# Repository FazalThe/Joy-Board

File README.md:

# Joy Board

A custom-built split keyboard with a built in thumb joystick on the left side, runs on zmk firmware and also supports zmk studio. The joystick is inteded to use the movements as key presses, but later is when I realised that it's really good for gaming( I don't really game, maybe thats why).

---

##  Features

-  Split Ergonomic Layout
- Thumb Joystick (Left Side)
- ZMK Studio 

---

## Schematic

---

##  PCB 

---

## Case

## BOM
- 2x Pro Micro nRF52840
- 50 x 1N5819 SMD Diodes
- 50 x MX-Style switches (and keycaps)
- 1  x COM-09032
- 2  x JST PH 2pin
- 8  x 10k ohm 0805 resistor
- 4  x 22k ohm 0805 resistor
- 4  x 2.4k ohm 0805 resistor
- 4  x LM339 - SOIC14
- 2  x 100-400 MaH li-po battery
- 4  x 4mm M2 Heatset insert
- 14 x 6mm M2 Heatset insert
- 4  x 6mm M2 Screws
- 14 x 8mm M2 Screws

---

## Credits

- Cherry MX keycap 3D model from [GrabCAD](https://grabcad.com/library/cherry-mx-keycaps-1).

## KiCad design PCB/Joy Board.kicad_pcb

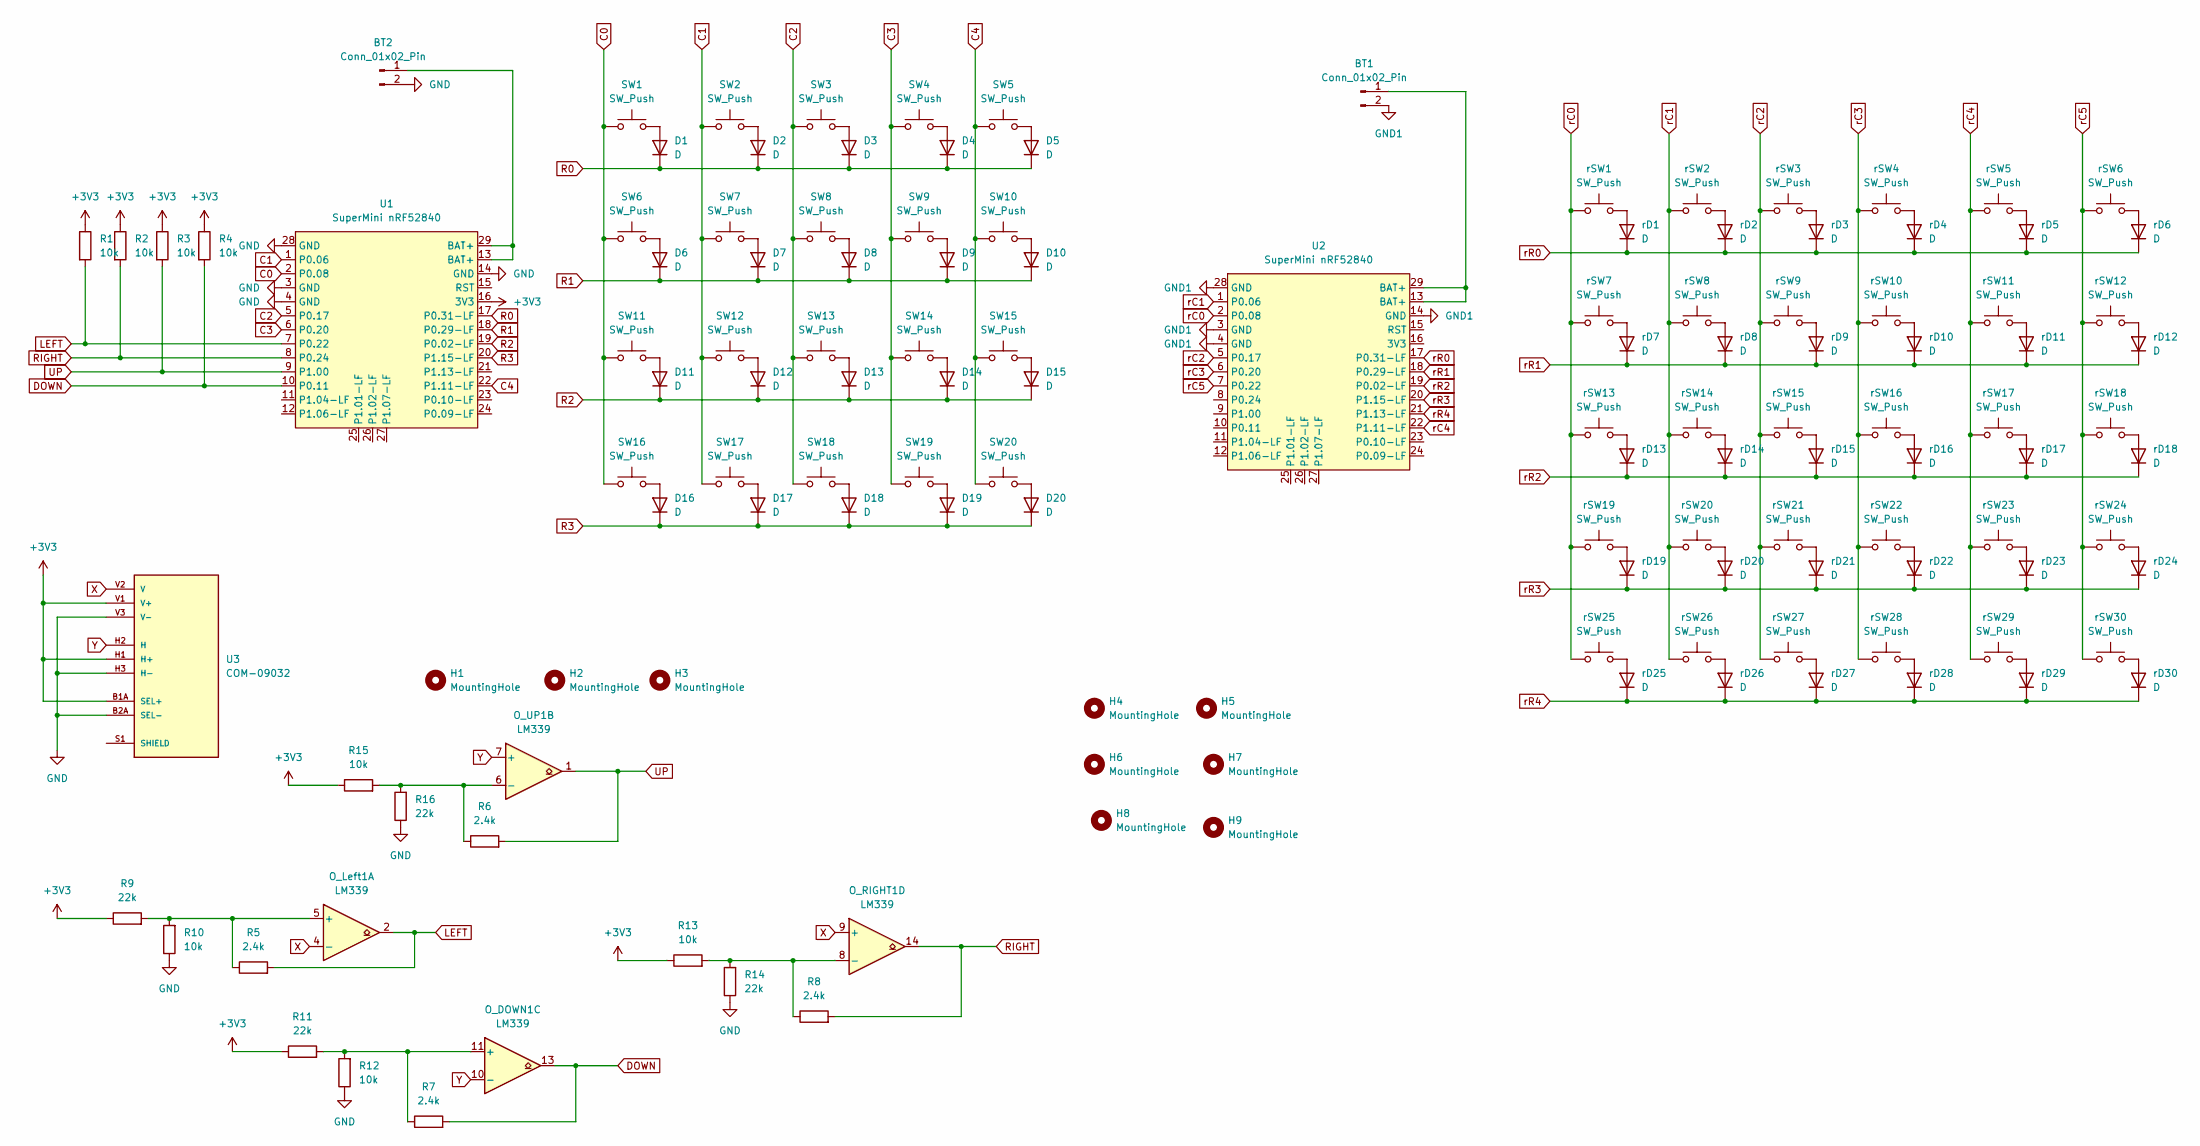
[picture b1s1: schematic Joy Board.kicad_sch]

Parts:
BT1, BT2: Conn_01x02_Pin; JST_PH_S2B-PH-K_1x02_P2.00mm_Horizontal
D1, D2, D3, D4, D5, D6, D7, D8, D9, D10, D11, D12, D13, D14, D15, D16, D17, D18, D19, D20: D; D_SOD-123
H1, H2, H3: MountingHole; mouse-bite-5mm-slot
H4, H5, H6, H7, H8, H9: MountingHole; MountingHole_2.2mm_M2
O_DOWN1: LM339; SOIC-14_3.9x8.7mm_P1.27mm
O_Left1: LM339; SOIC-14_3.9x8.7mm_P1.27mm
O_RIGHT1: LM339; SOIC-14_3.9x8.7mm_P1.27mm
O_UP1: LM339; SOIC-14_3.9x8.7mm_P1.27mm
R1, R2, R3, R4, R10, R12, R13, R15: 10k; R_0805_2012Metric_Pad1.20x1.40mm_HandSolder
R5, R6, R7, R8: 2.4k; R_0805_2012Metric_Pad1.20x1.40mm_HandSolder
R9, R11, R14, R16: 22k; R_0805_2012Metric_Pad1.20x1.40mm_HandSolder
SW1, SW2, SW3, SW4, SW5, SW6, SW7, SW8, SW9, SW10, SW11, SW12, SW13, SW14, SW15, SW16, SW17, SW18, SW19, SW20: SW_Push; SW_Cherry_MX_1.00u_PCB_3d
U1, U2: SuperMini nRF52840; SuperMini_nRF52840_AH_USBup
U3: COM-09032; XDCR_COM-09032; PARTREV N/A
rD1, rD2, rD3, rD4, rD5, rD6, rD7, rD8, rD9, rD10, rD11, rD12, rD13, rD14, rD15, rD16, rD17, rD18, rD19, rD20, rD21, rD22, rD23, rD24, rD25, rD26, rD27, rD28, rD29, rD30: D; D_SOD-123
rSW1, rSW2, rSW3, rSW4, rSW5, rSW6, rSW7, rSW8, rSW9, rSW10, rSW11, rSW12, rSW13, rSW14, rSW15, rSW16, rSW17, rSW18, rSW19, rSW20, rSW21, rSW22, rSW23, rSW24, rSW25, rSW26, rSW27, rSW28, rSW29: SW_Push; SW_Cherry_MX_1.00u_PCB_3d
rSW30: SW_Push; SW_Cherry_MX_1.50u_PCB

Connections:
+3V3: R1.1, R2.1, R3.1, R4.1, R9.1, R11.1, R13.1, R15.1, U1.16 (3V3), U3.B1A (SEL+), U3.H1 (H+), U3.V1 (V+)
C0: SW1.1, SW6.1, SW11.1, SW16.1, U1.2 (P0.08)
C1: SW2.1, SW7.1, SW12.1, SW17.1, U1.1 (P0.06)
C2: SW3.1, SW8.1, SW13.1, SW18.1, U1.5 (P0.17)
C3: SW4.1, SW9.1, SW14.1, SW19.1, U1.6 (P0.20)
C4: SW5.1, SW10.1, SW15.1, SW20.1, U1.22 (P1.11-LF)
DOWN: O_DOWN1.13, R4.2, R7.2, U1.10 (P0.11)
GND: BT2.2, R10.1, R12.1, R14.1, R16.1, U1.3 (GND), U1.4 (GND), U1.14 (GND), U1.28 (GND), U3.B2A (SEL-), U3.H3 (H-), U3.V3 (V-)
GND1: BT1.2, U2.3 (GND), U2.4 (GND), U2.14 (GND), U2.28 (GND)
LEFT: O_Left1.2, R1.2, R5.2, U1.7 (P0.22)
unnamed: BT1.1, U2.13 (BAT+), U2.29 (BAT+)
unnamed: BT2.1, U1.13 (BAT+), U1.29 (BAT+)
unnamed: D1.2 (A), SW1.2
unnamed: D2.2 (A), SW2.2
unnamed: D3.2 (A), SW3.2
unnamed: D4.2 (A), SW4.2
unnamed: D5.2 (A), SW5.2
unnamed: D6.2 (A), SW6.2
unnamed: D7.2 (A), SW7.2
unnamed: D8.2 (A), SW8.2
unnamed: D9.2 (A), SW9.2
unnamed: D10.2 (A), SW10.2
unnamed: D11.2 (A), SW11.2
unnamed: D12.2 (A), SW12.2
unnamed: D13.2 (A), SW13.2
unnamed: D14.2 (A), SW14.2
unnamed: D15.2 (A), SW15.2
unnamed: D16.2 (A), SW16.2
unnamed: D17.2 (A), SW17.2
unnamed: D18.2 (A), SW18.2
unnamed: D19.2 (A), SW19.2
unnamed: D20.2 (A), SW20.2
unnamed: O_DOWN1.11 (+), R7.1, R11.2, R12.2
unnamed: O_Left1.5 (+), R5.1, R9.2, R10.2
unnamed: O_RIGHT1.8 (-), R8.1, R13.2, R14.2
unnamed: O_UP1.6 (-), R6.1, R15.2, R16.2
unnamed: U3.S1 (SHIELD), U3.S2 (SHIELD), U3.S3 (SHIELD), U3.S4 (SHIELD)
unnamed: rD1.2 (A), rSW1.2
unnamed: rD2.2 (A), rSW2.2
unnamed: rD3.2 (A), rSW3.2
unnamed: rD4.2 (A), rSW4.2
unnamed: rD5.2 (A), rSW5.2
unnamed: rD6.2 (A), rSW6.2
unnamed: rD7.2 (A), rSW7.2
unnamed: rD8.2 (A), rSW8.2
unnamed: rD9.2 (A), rSW9.2
unnamed: rD10.2 (A), rSW10.2
unnamed: rD11.2 (A), rSW11.2
unnamed: rD12.2 (A), rSW12.2
unnamed: rD13.2 (A), rSW13.2
unnamed: rD14.2 (A), rSW14.2
unnamed: rD15.2 (A), rSW15.2
unnamed: rD16.2 (A), rSW16.2
unnamed: rD17.2 (A), rSW17.2
unnamed: rD18.2 (A), rSW18.2
unnamed: rD19.2 (A), rSW19.2
unnamed: rD20.2 (A), rSW20.2
unnamed: rD21.2 (A), rSW21.2
unnamed: rD22.2 (A), rSW22.2
unnamed: rD23.2 (A), rSW23.2
unnamed: rD24.2 (A), rSW24.2
unnamed: rD25.2 (A), rSW25.2
unnamed: rD26.2 (A), rSW26.2
unnamed: rD27.2 (A), rSW27.2
unnamed: rD28.2 (A), rSW28.2
unnamed: rD29.2 (A), rSW29.2
unnamed: rD30.2 (A), rSW30.2
R0: D1.1 (K), D2.1 (K), D3.1 (K), D4.1 (K), D5.1 (K), U1.17 (P0.31-LF)
R1: D6.1 (K), D7.1 (K), D8.1 (K), D9.1 (K), D10.1 (K), U1.18 (P0.29-LF)
R2: D11.1 (K), D12.1 (K), D13.1 (K), D14.1 (K), D15.1 (K), U1.19 (P0.02-LF)
R3: D16.1 (K), D17.1 (K), D18.1 (K), D19.1 (K), D20.1 (K), U1.20 (P1.15-LF)
RIGHT: O_RIGHT1.14, R2.2, R8.2, U1.8 (P0.24)
UP: O_UP1.1, R3.2, R6.2, U1.9 (P1.00)
X: O_Left1.4 (-), O_RIGHT1.9 (+), U3.V2 (V)
Y: O_DOWN1.10 (-), O_UP1.7 (+), U3.H2 (H)
rC0: U2.2 (P0.08), rSW1.1, rSW7.1, rSW13.1, rSW19.1, rSW25.1
rC1: U2.1 (P0.06), rSW2.1, rSW8.1, rSW14.1, rSW20.1, rSW26.1
rC2: U2.5 (P0.17), rSW3.1, rSW9.1, rSW15.1, rSW21.1, rSW27.1
rC3: U2.6 (P0.20), rSW4.1, rSW10.1, rSW16.1, rSW22.1, rSW28.1
rC4: U2.22 (P1.11-LF), rSW5.1, rSW11.1, rSW17.1, rSW23.1, rSW29.1
rC5: U2.7 (P0.22), rSW6.1, rSW12.1, rSW18.1, rSW24.1, rSW30.1
rR0: U2.17 (P0.31-LF), rD1.1 (K), rD2.1 (K), rD3.1 (K), rD4.1 (K), rD5.1 (K), rD6.1 (K)
rR1: U2.18 (P0.29-LF), rD7.1 (K), rD8.1 (K), rD9.1 (K), rD10.1 (K), rD11.1 (K), rD12.1 (K)
rR2: U2.19 (P0.02-LF), rD13.1 (K), rD14.1 (K), rD15.1 (K), rD16.1 (K), rD17.1 (K), rD18.1 (K)
rR3: U2.20 (P1.15-LF), rD19.1 (K), rD20.1 (K), rD21.1 (K), rD22.1 (K), rD23.1 (K), rD24.1 (K)
rR4: U2.21 (P1.13-LF), rD25.1 (K), rD26.1 (K), rD27.1 (K), rD28.1 (K), rD29.1 (K), rD30.1 (K)

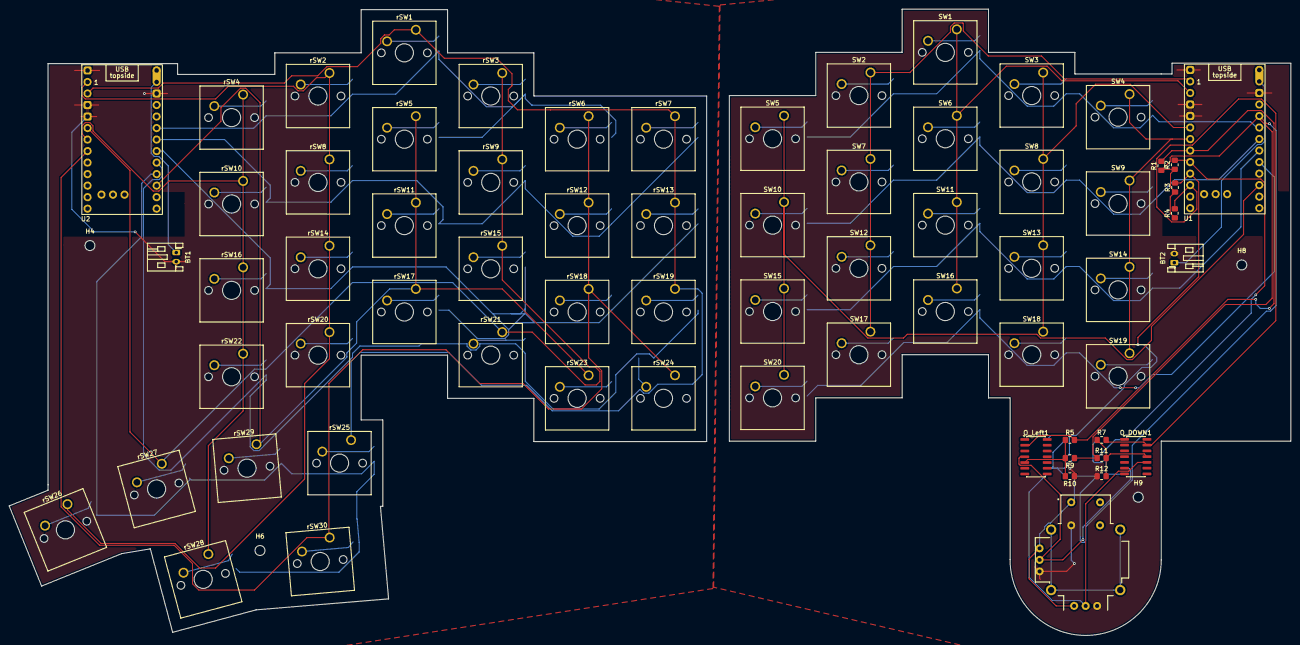
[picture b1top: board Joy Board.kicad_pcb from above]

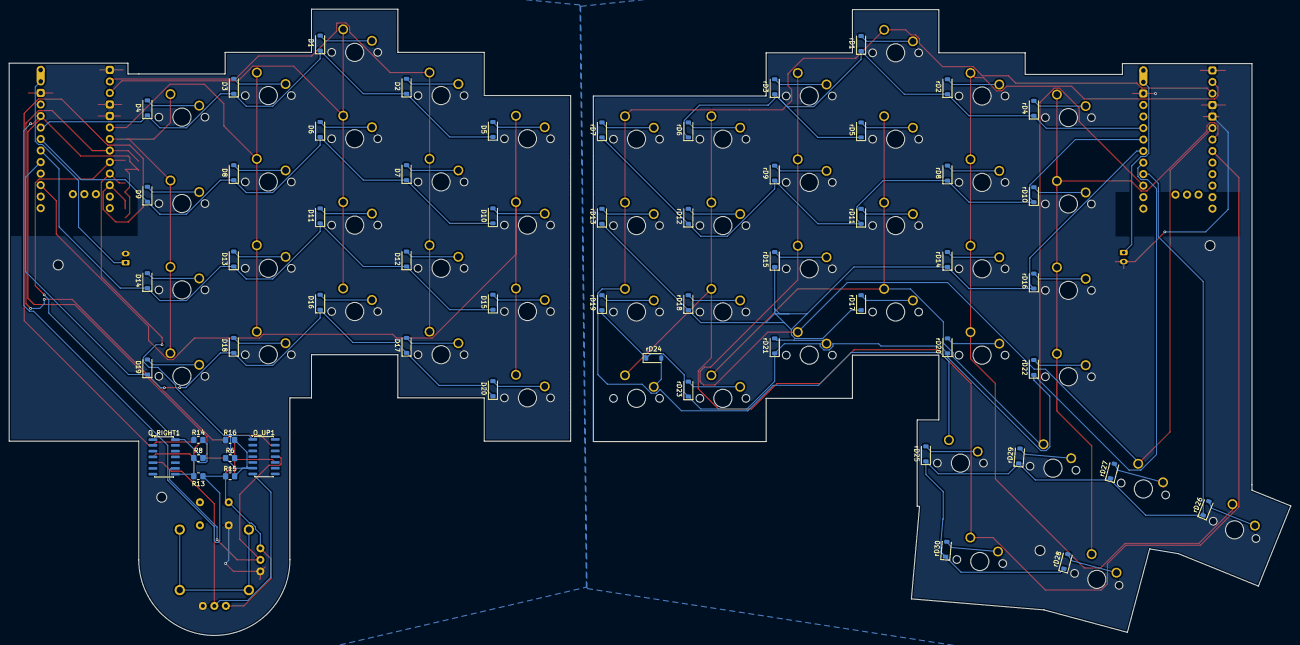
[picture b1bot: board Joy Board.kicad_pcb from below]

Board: 2 copper layers, 282.6 x 138.1 mm, 129 parts (58 on the bottom side), 86 nets.

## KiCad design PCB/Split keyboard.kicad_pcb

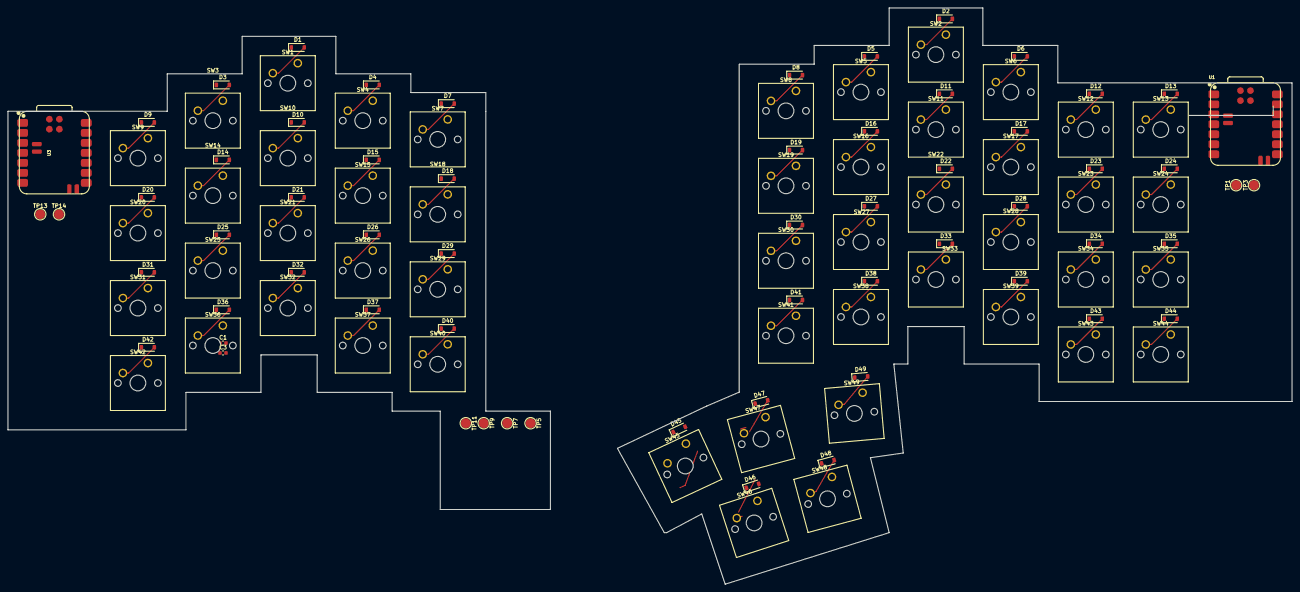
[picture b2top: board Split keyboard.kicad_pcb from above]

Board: 2 copper layers, 326.3 x 146.4 mm, 110 parts (0 on the bottom side), 74 nets.

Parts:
C1, C3: 100 nF; C_0603_1608Metric
D1, D2, D3, D4, D5, D6, D7, D8, D9, D10, D11, D12, D13, D14, D15, D16, D17, D18, D19, D20, D21, D22, D23, D24, D25, D26, D27, D28, D29, D30, D31, D32, D33, D34, D35, D36, D37, D38, D39, D40, D41, D42, D43, D44, D45, D46, D47, D48, D49: D; D_SOD-123
SW1, SW2, SW3, SW4, SW5, SW6, SW7, SW8, SW9, SW10, SW11, SW12, SW13, SW14, SW15, SW16, SW17, SW18, SW19, SW20, SW21, SW22, SW23, SW24, SW25, SW26, SW27, SW28, SW29, SW30, SW31, SW32, SW33, SW34, SW35, SW36, SW37, SW38, SW39, SW40, SW41, SW42, SW43, SW44, SW45, SW46, SW47, SW48, SW49: SW_Push; SW_Cherry_MX_1.00u_PCB
TP1, TP5, TP14: GND; TestPoint_Pad_D2.5mm
TP3, TP13: BAT; TestPoint_Pad_D2.5mm
TP7: VCC; TestPoint_Pad_D2.5mm
TP9: X; TestPoint_Pad_D2.5mm
TP11: Y; TestPoint_Pad_D2.5mm
U1, U3: XIAO-nRF52840-SMD

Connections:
+3V3: TP7.1, U1.12 (3V3), U3.12 (3V3)
C1: SW2.1, SW26.1, SW31.1, SW36.1, SW41.1, SW46.1, U3.1 (P0.02_A0_D0)
C2: SW4.1, SW27.1, SW32.1, SW37.1, SW42.1, SW47.1, U3.2 (P0.03_A1_D1)
C3: SW6.1, SW28.1, SW33.1, SW38.1, SW43.1, SW48.1, U3.3 (P0.28_A2_D2)
C4: SW8.1, SW29.1, SW34.1, SW39.1, SW44.1, SW49.1, U3.4 (P0.29_A3_D3)
C5: SW25.1, SW30.1, SW35.1, SW40.1, SW45.1, U3.5 (P0.04_A4_D4_SDA)
C10: SW1.1, SW10.1, SW15.1, SW20.1, U1.1 (P0.02_A0_D0)
C20: SW3.1, SW11.1, SW16.1, SW21.1, U1.2 (P0.03_A1_D1)
C30: SW5.1, SW12.1, SW17.1, SW22.1, U1.3 (P0.28_A2_D2)
C40: SW7.1, SW13.1, SW18.1, SW23.1, U1.4 (P0.29_A3_D3)
C50: SW9.1, SW14.1, SW19.1, SW24.1, U1.7 (P1.11_D6_TX)
GND: C1.1, C3.1, TP1.1, TP5.1, TP14.1, U1.16 (GND), U3.16 (GND)
unnamed: D1.2 (A), SW1.2
unnamed: D2.2 (A), SW2.2
unnamed: D3.2 (A), SW3.2
unnamed: D4.2 (A), SW4.2
unnamed: D5.2 (A), SW5.2
unnamed: D6.2 (A), SW6.2
unnamed: D7.2 (A), SW7.2
unnamed: D8.2 (A), SW8.2
unnamed: D9.2 (A), SW9.2
unnamed: D10.2 (A), SW10.2
unnamed: D11.2 (A), SW11.2
unnamed: D12.2 (A), SW12.2
unnamed: D13.2 (A), SW13.2
unnamed: D14.2 (A), SW14.2
unnamed: D15.2 (A), SW15.2
unnamed: D16.2 (A), SW16.2
unnamed: D17.2 (A), SW17.2
unnamed: D18.2 (A), SW18.2
unnamed: D19.2 (A), SW19.2
unnamed: D20.2 (A), SW20.2
unnamed: D21.2 (A), SW21.2
unnamed: D22.2 (A), SW22.2
unnamed: D23.2 (A), SW23.2
unnamed: D24.2 (A), SW24.2
unnamed: D25.2 (A), SW25.2
unnamed: D26.2 (A), SW26.2
unnamed: D27.2 (A), SW27.2
unnamed: D28.2 (A), SW28.2
unnamed: D29.2 (A), SW29.2
unnamed: D30.2 (A), SW30.2
unnamed: D31.2 (A), SW31.2
unnamed: D32.2 (A), SW32.2
unnamed: D33.2 (A), SW33.2
unnamed: D34.2 (A), SW34.2
unnamed: D35.2 (A), SW35.2
unnamed: D36.2 (A), SW36.2
unnamed: D37.2 (A), SW37.2
unnamed: D38.2 (A), SW38.2
unnamed: D39.2 (A), SW39.2
unnamed: D40.2 (A), SW40.2
unnamed: D41.2 (A), SW41.2
unnamed: D42.2 (A), SW42.2
unnamed: D43.2 (A), SW43.2
unnamed: D44.2 (A), SW44.2
unnamed: D45.2 (A), SW45.2
unnamed: D46.2 (A), SW46.2
unnamed: D47.2 (A), SW47.2
unnamed: D48.2 (A), SW48.2
unnamed: D49.2 (A), SW49.2
R1: D2.1 (K), D4.1 (K), D6.1 (K), D8.1 (K), D25.1 (K), U3.11 (P1.15_D10_MOSI)
R2: D26.1 (K), D27.1 (K), D28.1 (K), D29.1 (K), D30.1 (K), U3.10 (P1.14_D9_MISO)
R3: D31.1 (K), D32.1 (K), D33.1 (K), D34.1 (K), D35.1 (K), U3.9 (P1.13_D8_SCK)
R4: D36.1 (K), D37.1 (K), D38.1 (K), D39.1 (K), D40.1 (K), U3.8 (P1.12_D7_RX)
R5: D41.1 (K), D42.1 (K), D43.1 (K), D44.1 (K), D45.1 (K), U3.7 (P1.11_D6_TX)
R6: D46.1 (K), D47.1 (K), D48.1 (K), D49.1 (K), U3.6 (P0.05_A5_D5_SCL)
R10: D1.1 (K), D3.1 (K), D5.1 (K), D7.1 (K), D9.1 (K), U1.11 (P1.15_D10_MOSI)
R20: D10.1 (K), D11.1 (K), D12.1 (K), D13.1 (K), D14.1 (K), U1.10 (P1.14_D9_MISO)
R30: D15.1 (K), D16.1 (K), D17.1 (K), D18.1 (K), D19.1 (K), U1.9 (P1.13_D8_SCK)
R40: D20.1 (K), D21.1 (K), D22.1 (K), D23.1 (K), D24.1 (K), U1.8 (P1.12_D7_RX)
VBAT: TP3.1, TP13.1, U1.15 (BAT), U3.15 (BAT)
x: C1.2, TP9.1, U1.5 (P0.04_A4_D4_SDA)
y: C3.2, TP11.1, U1.6 (P0.05_A5_D5_SCL)

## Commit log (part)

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2026-03-31 Create README.md for Joy Board project
    Added initial README with project details and features.
2026-05-23 Revise README with detailed description and BOM
    Updated the README to enhance the description of the Joy Board and added a BOM section.
2026-05-23 init
2026-05-24 done
2026-05-24 really done
2026-05-24 last
2026-05-27 firmware done and updated to latest pcb
2026-05-28 pcb missing fixed
2026-05-28 BOM fix
2026-06-11 1st Re-submit
2026-06-11 Add schematic section to README
2026-06-23 Add credits section for Cherry MX keycap model
